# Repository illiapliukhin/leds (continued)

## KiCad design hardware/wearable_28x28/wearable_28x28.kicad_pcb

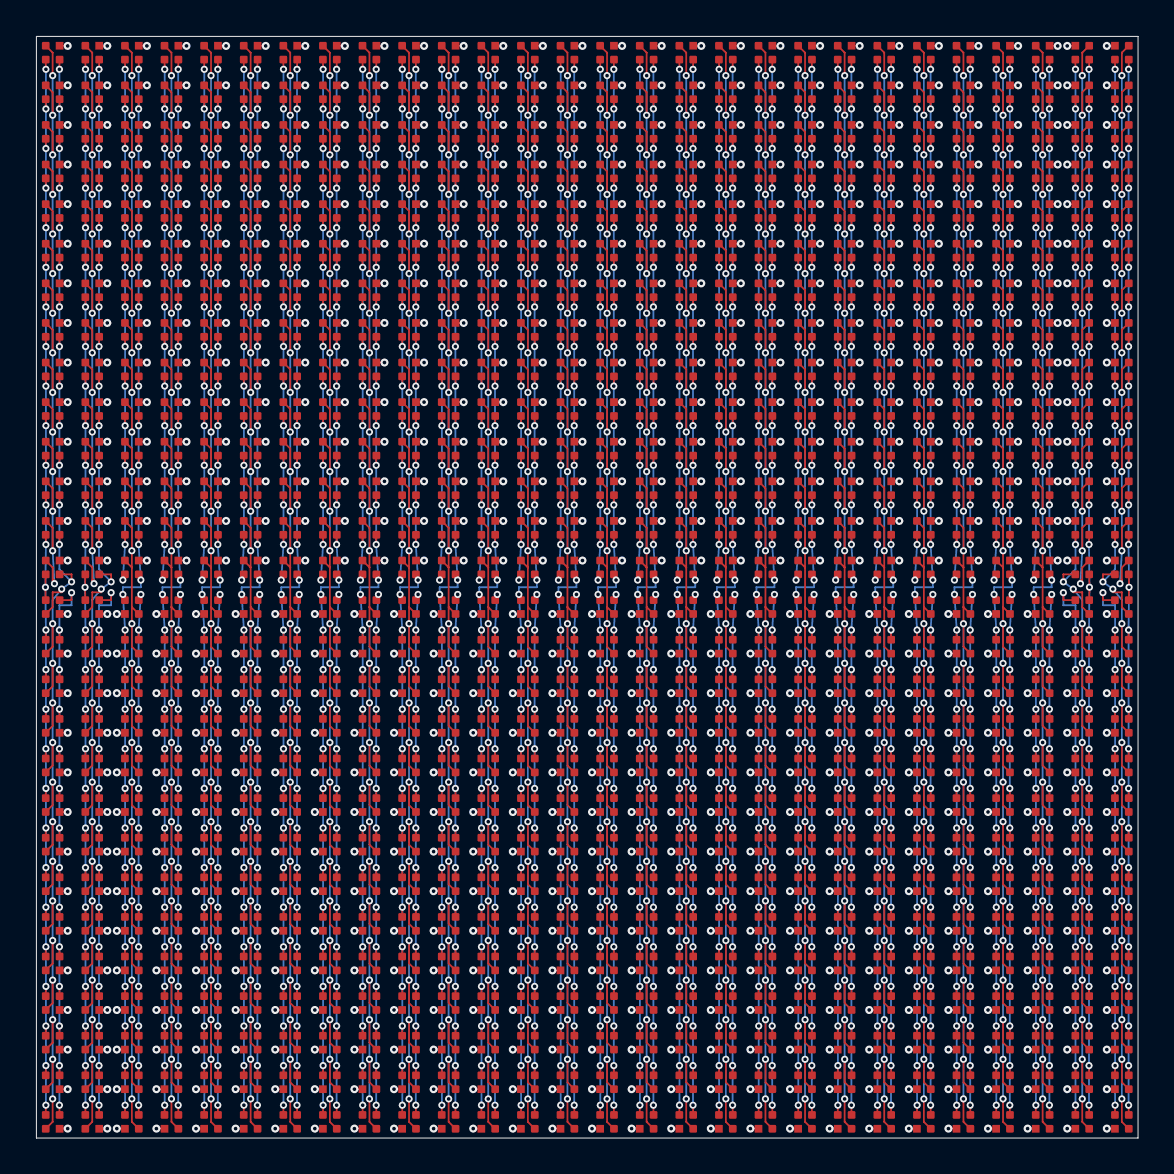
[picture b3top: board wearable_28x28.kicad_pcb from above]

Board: 4 copper layers, 61.2 x 61.2 mm, 784 parts (0 on the bottom side), 112 nets.

Parts:
D1, D2, D3, D4, D5, D6, D7, D8, D9, D10, D11, D12, D13, D14, D15, D16, D17, D18, D19, D20, D21, D22, D23, D24, D25, D26, D27, D28, D29, D30, D31, D32, D33, D34, D35, D36, D37, D38, D39, D40, D41, D42, D43, D44, D45, D46, D47, D48, D49, D50, D51, D52, D53, D54, D55, D56, D57, D58, D59, D60, D61, D62, D63, D64, D65, D66, D67, D68, D69, D70, D71, D72, D73, D74, D75, D76, D77, D78, D79, D80, D81, D82, D83, D84, D85, D86, D87, D88, D89, D90, D91, D92, D93, D94, D95, D96, D97, D98, D99, D100, D101, D102, D103, D104, D105, D106, D107, D108, D109, D110, D111, D112, D113, D114, D115, D116, D117, D118, D119, D120, D121, D122, D123, D124, D125, D126, D127, D128, D129, D130, D131, D132, D133, D134, D135, D136, D137, D138, D139, D140, D141, D142, D143, D144, D145, D146, D147, D148, D149, D150, D151, D152, D153, D154, D155, D156, D157, D158, D159, D160, D161, D162, D163, D164, D165, D166, D167, D168, D169, D170, D171, D172, D173, D174, D175, D176, D177, D178, D179, D180, D181, D182, D183, D184, D185, D186, D187, D188, D189, D190, D191, D192, D193, D194, D195, D196, D197, D198, D199, D200, D201, D202, D203, D204, D205, D206, D207, D208, D209, D210, D211, D212, D213, D214, D215, D216, D217, D218, D219, D220, D221, D222, D223, D224, D225, D226, D227, D228, D229, D230, D231, D232, D233, D234, D235, D236, D237, D238, D239, D240, D241, D242, D243, D244, D245, D246, D247, D248, D249, D250, D251, D252, D253, D254, D255, D256, D257, D258, D259, D260, D261, D262, D263, D264, D265, D266, D267, D268, D269, D270, D271, D272, D273, D274, D275, D276, D277, D278, D279, D280, D281, D282, D283, D284, D285, D286, D287, D288, D289, D290, D291, D292, D293, D294, D295, D296, D297, D298, D299, D300, D301, D302, D303, D304, D305, D306, D307, D308, D309, D310, D311, D312, D313, D314, D315, D316, D317, D318, D319, D320, D321, D322, D323, D324, D325, D326, D327, D328, D329, D330, D331, D332, D333, D334, D335, D336, D337, D338, D339, D340, D341, D342, D343, D344, D345, D346, D347, D348, D349, D350, D351, D352, D353, D354, D355, D356, D357, D358, D359, D360, D361, D362, D363, D364, D365, D366, D367, D368, D369, D370, D371, D372, D373, D374, D375, D376, D377, D378, D379, D380, D381, D382, D383, D384, D385, D386, D387, D388, D389, D390, D391, D392, D393, D394, D395, D396, D397, D398, D399, D400, D401, D402, D403, D404, D405, D406, D407, D408, D409, D410, D411, D412, D413, D414, D415, D416, D417, D418, D419, D420, D421, D422, D423, D424, D425, D426, D427, D428, D429, D430, D431, D432, D433, D434, D435, D436, D437, D438, D439, D440, D441, D442, D443, D444, D445, D446, D447, D448, D449, D450, D451, D452, D453, D454, D455, D456, D457, D458, D459, D460, D461, D462, D463, D464, D465, D466, D467, D468, D469, D470, D471, D472, D473, D474, D475, D476, D477, D478, D479, D480, D481, D482, D483, D484, D485, D486, D487, D488, D489, D490, D491, D492, D493, D494, D495, D496, D497, D498, D499, D500, D501, D502, D503, D504, D505, D506, D507, D508, D509, D510, D511, D512, D513, D514, D515, D516, D517, D518, D519, D520, D521, D522, D523, D524, D525, D526, D527, D528, D529, D530, D531, D532, D533, D534, D535, D536, D537, D538, D539, D540, D541, D542, D543, D544, D545, D546, D547, D548, D549, D550, D551, D552, D553, D554, D555, D556, D557, D558, D559, D560, D561, D562, D563, D564, D565, D566, D567, D568, D569, D570, D571, D572, D573, D574, D575, D576, D577, D578, D579, D580, D581, D582, D583, D584, D585, D586, D587, D588, D589, D590, D591, D592, D593, D594, D595, D596, D597, D598, D599, D600, D601, D602, D603, D604, D605, D606, D607, D608, D609, D610, D611, D612, D613, D614, D615, D616, D617, D618, D619, D620, D621, D622, D623, D624, D625, D626, D627, D628, D629, D630, D631, D632, D633, D634, D635, D636, D637, D638, D639, D640, D641, D642, D643, D644, D645, D646, D647, D648, D649, D650, D651, D652, D653, D654, D655, D656, D657, D658, D659, D660, D661, D662, D663, D664, D665, D666, D667, D668, D669, D670, D671, D672, D673, D674, D675, D676, D677, D678, D679, D680, D681, D682, D683, D684, D685, D686, D687, D688, D689, D690, D691, D692, D693, D694, D695, D696, D697, D698, D699, D700, D701, D702, D703, D704, D705, D706, D707, D708, D709, D710, D711, D712, D713, D714, D715, D716, D717, D718, D719, D720, D721, D722, D723, D724, D725, D726, D727, D728, D729, D730, D731, D732, D733, D734, D735, D736, D737, D738, D739, D740, D741, D742, D743, D744, D745, D746, D747, D748, D749, D750, D751, D752, D753, D754, D755, D756, D757, D758, D759, D760, D761, D762, D763, D764, D765, D766, D767, D768, D769, D770, D771, D772, D773, D774, D775, D776, D777, D778, D779, D780, D781, D782, D783, D784: MHPA1010RGBDT

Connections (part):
COL_B_01: D1.4 (K_B), D29.4 (K_B), D57.4 (K_B), D85.4 (K_B), D113.4 (K_B), D141.4 (K_B), D169.4 (K_B), D197.4 (K_B), D225.4 (K_B), D253.4 (K_B), D281.4 (K_B), D309.4 (K_B), D337.4 (K_B), D365.4 (K_B), D393.4 (K_B), D421.4 (K_B), D449.4 (K_B), D477.4 (K_B), D505.4 (K_B), D533.4 (K_B), D561.4 (K_B), D589.4 (K_B), D617.4 (K_B), D645.4 (K_B), D673.4 (K_B), D701.4 (K_B), D729.4 (K_B), D757.4 (K_B)
COL_B_02: D2.4 (K_B), D30.4 (K_B), D58.4 (K_B), D86.4 (K_B), D114.4 (K_B), D142.4 (K_B), D170.4 (K_B), D198.4 (K_B), D226.4 (K_B), D254.4 (K_B), D282.4 (K_B), D310.4 (K_B), D338.4 (K_B), D366.4 (K_B), D394.4 (K_B), D422.4 (K_B), D450.4 (K_B), D478.4 (K_B), D506.4 (K_B), D534.4 (K_B), D562.4 (K_B), D590.4 (K_B), D618.4 (K_B), D646.4 (K_B), D674.4 (K_B), D702.4 (K_B), D730.4 (K_B), D758.4 (K_B)
COL_B_03: D3.4 (K_B), D31.4 (K_B), D59.4 (K_B), D87.4 (K_B), D115.4 (K_B), D143.4 (K_B), D171.4 (K_B), D199.4 (K_B), D227.4 (K_B), D255.4 (K_B), D283.4 (K_B), D311.4 (K_B), D339.4 (K_B), D367.4 (K_B), D395.4 (K_B), D423.4 (K_B), D451.4 (K_B), D479.4 (K_B), D507.4 (K_B), D535.4 (K_B), D563.4 (K_B), D591.4 (K_B), D619.4 (K_B), D647.4 (K_B), D675.4 (K_B), D703.4 (K_B), D731.4 (K_B), D759.4 (K_B)
COL_B_04: D4.4 (K_B), D32.4 (K_B), D60.4 (K_B), D88.4 (K_B), D116.4 (K_B), D144.4 (K_B), D172.4 (K_B), D200.4 (K_B), D228.4 (K_B), D256.4 (K_B), D284.4 (K_B), D312.4 (K_B), D340.4 (K_B), D368.4 (K_B), D396.4 (K_B), D424.4 (K_B), D452.4 (K_B), D480.4 (K_B), D508.4 (K_B), D536.4 (K_B), D564.4 (K_B), D592.4 (K_B), D620.4 (K_B), D648.4 (K_B), D676.4 (K_B), D704.4 (K_B), D732.4 (K_B), D760.4 (K_B)
COL_B_05: D5.4 (K_B), D33.4 (K_B), D61.4 (K_B), D89.4 (K_B), D117.4 (K_B), D145.4 (K_B), D173.4 (K_B), D201.4 (K_B), D229.4 (K_B), D257.4 (K_B), D285.4 (K_B), D313.4 (K_B), D341.4 (K_B), D369.4 (K_B), D397.4 (K_B), D425.4 (K_B), D453.4 (K_B), D481.4 (K_B), D509.4 (K_B), D537.4 (K_B), D565.4 (K_B), D593.4 (K_B), D621.4 (K_B), D649.4 (K_B), D677.4 (K_B), D705.4 (K_B), D733.4 (K_B), D761.4 (K_B)
COL_B_06: D6.4 (K_B), D34.4 (K_B), D62.4 (K_B), D90.4 (K_B), D118.4 (K_B), D146.4 (K_B), D174.4 (K_B), D202.4 (K_B), D230.4 (K_B), D258.4 (K_B), D286.4 (K_B), D314.4 (K_B), D342.4 (K_B), D370.4 (K_B), D398.4 (K_B), D426.4 (K_B), D454.4 (K_B), D482.4 (K_B), D510.4 (K_B), D538.4 (K_B), D566.4 (K_B), D594.4 (K_B), D622.4 (K_B), D650.4 (K_B), D678.4 (K_B), D706.4 (K_B), D734.4 (K_B), D762.4 (K_B)
COL_B_07: D7.4 (K_B), D35.4 (K_B), D63.4 (K_B), D91.4 (K_B), D119.4 (K_B), D147.4 (K_B), D175.4 (K_B), D203.4 (K_B), D231.4 (K_B), D259.4 (K_B), D287.4 (K_B), D315.4 (K_B), D343.4 (K_B), D371.4 (K_B), D399.4 (K_B), D427.4 (K_B), D455.4 (K_B), D483.4 (K_B), D511.4 (K_B), D539.4 (K_B), D567.4 (K_B), D595.4 (K_B), D623.4 (K_B), D651.4 (K_B), D679.4 (K_B), D707.4 (K_B), D735.4 (K_B), D763.4 (K_B)
COL_B_08: D8.4 (K_B), D36.4 (K_B), D64.4 (K_B), D92.4 (K_B), D120.4 (K_B), D148.4 (K_B), D176.4 (K_B), D204.4 (K_B), D232.4 (K_B), D260.4 (K_B), D288.4 (K_B), D316.4 (K_B), D344.4 (K_B), D372.4 (K_B), D400.4 (K_B), D428.4 (K_B), D456.4 (K_B), D484.4 (K_B), D512.4 (K_B), D540.4 (K_B), D568.4 (K_B), D596.4 (K_B), D624.4 (K_B), D652.4 (K_B), D680.4 (K_B), D708.4 (K_B), D736.4 (K_B), D764.4 (K_B)
COL_B_09: D9.4 (K_B), D37.4 (K_B), D65.4 (K_B), D93.4 (K_B), D121.4 (K_B), D149.4 (K_B), D177.4 (K_B), D205.4 (K_B), D233.4 (K_B), D261.4 (K_B), D289.4 (K_B), D317.4 (K_B), D345.4 (K_B), D373.4 (K_B), D401.4 (K_B), D429.4 (K_B), D457.4 (K_B), D485.4 (K_B), D513.4 (K_B), D541.4 (K_B), D569.4 (K_B), D597.4 (K_B), D625.4 (K_B), D653.4 (K_B), D681.4 (K_B), D709.4 (K_B), D737.4 (K_B), D765.4 (K_B)
COL_B_10: D10.4 (K_B), D38.4 (K_B), D66.4 (K_B), D94.4 (K_B), D122.4 (K_B), D150.4 (K_B), D178.4 (K_B), D206.4 (K_B), D234.4 (K_B), D262.4 (K_B), D290.4 (K_B), D318.4 (K_B), D346.4 (K_B), D374.4 (K_B), D402.4 (K_B), D430.4 (K_B), D458.4 (K_B), D486.4 (K_B), D514.4 (K_B), D542.4 (K_B), D570.4 (K_B), D598.4 (K_B), D626.4 (K_B), D654.4 (K_B), D682.4 (K_B), D710.4 (K_B), D738.4 (K_B), D766.4 (K_B)
COL_B_11: D11.4 (K_B), D39.4 (K_B), D67.4 (K_B), D95.4 (K_B), D123.4 (K_B), D151.4 (K_B), D179.4 (K_B), D207.4 (K_B), D235.4 (K_B), D263.4 (K_B), D291.4 (K_B), D319.4 (K_B), D347.4 (K_B), D375.4 (K_B), D403.4 (K_B), D431.4 (K_B), D459.4 (K_B), D487.4 (K_B), D515.4 (K_B), D543.4 (K_B), D571.4 (K_B), D599.4 (K_B), D627.4 (K_B), D655.4 (K_B), D683.4 (K_B), D711.4 (K_B), D739.4 (K_B), D767.4 (K_B)
COL_B_12: D12.4 (K_B), D40.4 (K_B), D68.4 (K_B), D96.4 (K_B), D124.4 (K_B), D152.4 (K_B), D180.4 (K_B), D208.4 (K_B), D236.4 (K_B), D264.4 (K_B), D292.4 (K_B), D320.4 (K_B), D348.4 (K_B), D376.4 (K_B), D404.4 (K_B), D432.4 (K_B), D460.4 (K_B), D488.4 (K_B), D516.4 (K_B), D544.4 (K_B), D572.4 (K_B), D600.4 (K_B), D628.4 (K_B), D656.4 (K_B), D684.4 (K_B), D712.4 (K_B), D740.4 (K_B), D768.4 (K_B)
COL_B_13: D13.4 (K_B), D41.4 (K_B), D69.4 (K_B), D97.4 (K_B), D125.4 (K_B), D153.4 (K_B), D181.4 (K_B), D209.4 (K_B), D237.4 (K_B), D265.4 (K_B), D293.4 (K_B), D321.4 (K_B), D349.4 (K_B), D377.4 (K_B), D405.4 (K_B), D433.4 (K_B), D461.4 (K_B), D489.4 (K_B), D517.4 (K_B), D545.4 (K_B), D573.4 (K_B), D601.4 (K_B), D629.4 (K_B), D657.4 (K_B), D685.4 (K_B), D713.4 (K_B), D741.4 (K_B), D769.4 (K_B)
COL_B_14: D14.4 (K_B), D42.4 (K_B), D70.4 (K_B), D98.4 (K_B), D126.4 (K_B), D154.4 (K_B), D182.4 (K_B), D210.4 (K_B), D238.4 (K_B), D266.4 (K_B), D294.4 (K_B), D322.4 (K_B), D350.4 (K_B), D378.4 (K_B), D406.4 (K_B), D434.4 (K_B), D462.4 (K_B), D490.4 (K_B), D518.4 (K_B), D546.4 (K_B), D574.4 (K_B), D602.4 (K_B), D630.4 (K_B), D658.4 (K_B), D686.4 (K_B), D714.4 (K_B), D742.4 (K_B), D770.4 (K_B)
COL_B_15: D15.4 (K_B), D43.4 (K_B), D71.4 (K_B), D99.4 (K_B), D127.4 (K_B), D155.4 (K_B), D183.4 (K_B), D211.4 (K_B), D239.4 (K_B), D267.4 (K_B), D295.4 (K_B), D323.4 (K_B), D351.4 (K_B), D379.4 (K_B), D407.4 (K_B), D435.4 (K_B), D463.4 (K_B), D491.4 (K_B), D519.4 (K_B), D547.4 (K_B), D575.4 (K_B), D603.4 (K_B), D631.4 (K_B), D659.4 (K_B), D687.4 (K_B), D715.4 (K_B), D743.4 (K_B), D771.4 (K_B)
COL_B_16: D16.4 (K_B), D44.4 (K_B), D72.4 (K_B), D100.4 (K_B), D128.4 (K_B), D156.4 (K_B), D184.4 (K_B), D212.4 (K_B), D240.4 (K_B), D268.4 (K_B), D296.4 (K_B), D324.4 (K_B), D352.4 (K_B), D380.4 (K_B), D408.4 (K_B), D436.4 (K_B), D464.4 (K_B), D492.4 (K_B), D520.4 (K_B), D548.4 (K_B), D576.4 (K_B), D604.4 (K_B), D632.4 (K_B), D660.4 (K_B), D688.4 (K_B), D716.4 (K_B), D744.4 (K_B), D772.4 (K_B)
COL_B_17: D17.4 (K_B), D45.4 (K_B), D73.4 (K_B), D101.4 (K_B), D129.4 (K_B), D157.4 (K_B), D185.4 (K_B), D213.4 (K_B), D241.4 (K_B), D269.4 (K_B), D297.4 (K_B), D325.4 (K_B), D353.4 (K_B), D381.4 (K_B), D409.4 (K_B), D437.4 (K_B), D465.4 (K_B), D493.4 (K_B), D521.4 (K_B), D549.4 (K_B), D577.4 (K_B), D605.4 (K_B), D633.4 (K_B), D661.4 (K_B), D689.4 (K_B), D717.4 (K_B), D745.4 (K_B), D773.4 (K_B)
COL_B_18: D18.4 (K_B), D46.4 (K_B), D74.4 (K_B), D102.4 (K_B), D130.4 (K_B), D158.4 (K_B), D186.4 (K_B), D214.4 (K_B), D242.4 (K_B), D270.4 (K_B), D298.4 (K_B), D326.4 (K_B), D354.4 (K_B), D382.4 (K_B), D410.4 (K_B), D438.4 (K_B), D466.4 (K_B), D494.4 (K_B), D522.4 (K_B), D550.4 (K_B), D578.4 (K_B), D606.4 (K_B), D634.4 (K_B), D662.4 (K_B), D690.4 (K_B), D718.4 (K_B), D746.4 (K_B), D774.4 (K_B)
COL_B_19: D19.4 (K_B), D47.4 (K_B), D75.4 (K_B), D103.4 (K_B), D131.4 (K_B), D159.4 (K_B), D187.4 (K_B), D215.4 (K_B), D243.4 (K_B), D271.4 (K_B), D299.4 (K_B), D327.4 (K_B), D355.4 (K_B), D383.4 (K_B), D411.4 (K_B), D439.4 (K_B), D467.4 (K_B), D495.4 (K_B), D523.4 (K_B), D551.4 (K_B), D579.4 (K_B), D607.4 (K_B), D635.4 (K_B), D663.4 (K_B), D691.4 (K_B), D719.4 (K_B), D747.4 (K_B), D775.4 (K_B)
COL_B_20: D20.4 (K_B), D48.4 (K_B), D76.4 (K_B), D104.4 (K_B), D132.4 (K_B), D160.4 (K_B), D188.4 (K_B), D216.4 (K_B), D244.4 (K_B), D272.4 (K_B), D300.4 (K_B), D328.4 (K_B), D356.4 (K_B), D384.4 (K_B), D412.4 (K_B), D440.4 (K_B), D468.4 (K_B), D496.4 (K_B), D524.4 (K_B), D552.4 (K_B), D580.4 (K_B), D608.4 (K_B), D636.4 (K_B), D664.4 (K_B), D692.4 (K_B), D720.4 (K_B), D748.4 (K_B), D776.4 (K_B)
COL_B_21: D21.4 (K_B), D49.4 (K_B), D77.4 (K_B), D105.4 (K_B), D133.4 (K_B), D161.4 (K_B), D189.4 (K_B), D217.4 (K_B), D245.4 (K_B), D273.4 (K_B), D301.4 (K_B), D329.4 (K_B), D357.4 (K_B), D385.4 (K_B), D413.4 (K_B), D441.4 (K_B), D469.4 (K_B), D497.4 (K_B), D525.4 (K_B), D553.4 (K_B), D581.4 (K_B), D609.4 (K_B), D637.4 (K_B), D665.4 (K_B), D693.4 (K_B), D721.4 (K_B), D749.4 (K_B), D777.4 (K_B)
COL_B_22: D22.4 (K_B), D50.4 (K_B), D78.4 (K_B), D106.4 (K_B), D134.4 (K_B), D162.4 (K_B), D190.4 (K_B), D218.4 (K_B), D246.4 (K_B), D274.4 (K_B), D302.4 (K_B), D330.4 (K_B), D358.4 (K_B), D386.4 (K_B), D414.4 (K_B), D442.4 (K_B), D470.4 (K_B), D498.4 (K_B), D526.4 (K_B), D554.4 (K_B), D582.4 (K_B), D610.4 (K_B), D638.4 (K_B), D666.4 (K_B), D694.4 (K_B), D722.4 (K_B), D750.4 (K_B), D778.4 (K_B)
COL_B_23: D23.4 (K_B), D51.4 (K_B), D79.4 (K_B), D107.4 (K_B), D135.4 (K_B), D163.4 (K_B), D191.4 (K_B), D219.4 (K_B), D247.4 (K_B), D275.4 (K_B), D303.4 (K_B), D331.4 (K_B), D359.4 (K_B), D387.4 (K_B), D415.4 (K_B), D443.4 (K_B), D471.4 (K_B), D499.4 (K_B), D527.4 (K_B), D555.4 (K_B), D583.4 (K_B), D611.4 (K_B), D639.4 (K_B), D667.4 (K_B), D695.4 (K_B), D723.4 (K_B), D751.4 (K_B), D779.4 (K_B)
COL_B_24: D24.4 (K_B), D52.4 (K_B), D80.4 (K_B), D108.4 (K_B), D136.4 (K_B), D164.4 (K_B), D192.4 (K_B), D220.4 (K_B), D248.4 (K_B), D276.4 (K_B), D304.4 (K_B), D332.4 (K_B), D360.4 (K_B), D388.4 (K_B), D416.4 (K_B), D444.4 (K_B), D472.4 (K_B), D500.4 (K_B), D528.4 (K_B), D556.4 (K_B), D584.4 (K_B), D612.4 (K_B), D640.4 (K_B), D668.4 (K_B), D696.4 (K_B), D724.4 (K_B), D752.4 (K_B), D780.4 (K_B)
COL_B_25: D25.4 (K_B), D53.4 (K_B), D81.4 (K_B), D109.4 (K_B), D137.4 (K_B), D165.4 (K_B), D193.4 (K_B), D221.4 (K_B), D249.4 (K_B), D277.4 (K_B), D305.4 (K_B), D333.4 (K_B), D361.4 (K_B), D389.4 (K_B), D417.4 (K_B), D445.4 (K_B), D473.4 (K_B), D501.4 (K_B), D529.4 (K_B), D557.4 (K_B), D585.4 (K_B), D613.4 (K_B), D641.4 (K_B), D669.4 (K_B), D697.4 (K_B), D725.4 (K_B), D753.4 (K_B), D781.4 (K_B)
COL_B_26: D26.4 (K_B), D54.4 (K_B), D82.4 (K_B), D110.4 (K_B), D138.4 (K_B), D166.4 (K_B), D194.4 (K_B), D222.4 (K_B), D250.4 (K_B), D278.4 (K_B), D306.4 (K_B), D334.4 (K_B), D362.4 (K_B), D390.4 (K_B), D418.4 (K_B), D446.4 (K_B), D474.4 (K_B), D502.4 (K_B), D530.4 (K_B), D558.4 (K_B), D586.4 (K_B), D614.4 (K_B), D642.4 (K_B), D670.4 (K_B), D698.4 (K_B), D726.4 (K_B), D754.4 (K_B), D782.4 (K_B)
COL_B_27: D27.4 (K_B), D55.4 (K_B), D83.4 (K_B), D111.4 (K_B), D139.4 (K_B), D167.4 (K_B), D195.4 (K_B), D223.4 (K_B), D251.4 (K_B), D279.4 (K_B), D307.4 (K_B), D335.4 (K_B), D363.4 (K_B), D391.4 (K_B), D419.4 (K_B), D447.4 (K_B), D475.4 (K_B), D503.4 (K_B), D531.4 (K_B), D559.4 (K_B), D587.4 (K_B), D615.4 (K_B), D643.4 (K_B), D671.4 (K_B), D699.4 (K_B), D727.4 (K_B), D755.4 (K_B), D783.4 (K_B)
COL_B_28: D28.4 (K_B), D56.4 (K_B), D84.4 (K_B), D112.4 (K_B), D140.4 (K_B), D168.4 (K_B), D196.4 (K_B), D224.4 (K_B), D252.4 (K_B), D280.4 (K_B), D308.4 (K_B), D336.4 (K_B), D364.4 (K_B), D392.4 (K_B), D420.4 (K_B), D448.4 (K_B), D476.4 (K_B), D504.4 (K_B), D532.4 (K_B), D560.4 (K_B), D588.4 (K_B), D616.4 (K_B), D644.4 (K_B), D672.4 (K_B), D700.4 (K_B), D728.4 (K_B), D756.4 (K_B), D784.4 (K_B)
COL_G_01: D1.3 (K_G), D29.3 (K_G), D57.3 (K_G), D85.3 (K_G), D113.3 (K_G), D141.3 (K_G), D169.3 (K_G), D197.3 (K_G), D225.3 (K_G), D253.3 (K_G), D281.3 (K_G), D309.3 (K_G), D337.3 (K_G), D365.3 (K_G), D393.3 (K_G), D421.3 (K_G), D449.3 (K_G), D477.3 (K_G), D505.3 (K_G), D533.3 (K_G), D561.3 (K_G), D589.3 (K_G), D617.3 (K_G), D645.3 (K_G), D673.3 (K_G), D701.3 (K_G), D729.3 (K_G), D757.3 (K_G)
COL_G_02: D2.3 (K_G), D30.3 (K_G), D58.3 (K_G), D86.3 (K_G), D114.3 (K_G), D142.3 (K_G), D170.3 (K_G), D198.3 (K_G), D226.3 (K_G), D254.3 (K_G), D282.3 (K_G), D310.3 (K_G), D338.3 (K_G), D366.3 (K_G), D394.3 (K_G), D422.3 (K_G), D450.3 (K_G), D478.3 (K_G), D506.3 (K_G), D534.3 (K_G), D562.3 (K_G), D590.3 (K_G), D618.3 (K_G), D646.3 (K_G), D674.3 (K_G), D702.3 (K_G), D730.3 (K_G), D758.3 (K_G)
COL_G_03: D3.3 (K_G), D31.3 (K_G), D59.3 (K_G), D87.3 (K_G), D115.3 (K_G), D143.3 (K_G), D171.3 (K_G), D199.3 (K_G), D227.3 (K_G), D255.3 (K_G), D283.3 (K_G), D311.3 (K_G), D339.3 (K_G), D367.3 (K_G), D395.3 (K_G), D423.3 (K_G), D451.3 (K_G), D479.3 (K_G), D507.3 (K_G), D535.3 (K_G), D563.3 (K_G), D591.3 (K_G), D619.3 (K_G), D647.3 (K_G), D675.3 (K_G), D703.3 (K_G), D731.3 (K_G), D759.3 (K_G)
COL_G_04: D4.3 (K_G), D32.3 (K_G), D60.3 (K_G), D88.3 (K_G), D116.3 (K_G), D144.3 (K_G), D172.3 (K_G), D200.3 (K_G), D228.3 (K_G), D256.3 (K_G), D284.3 (K_G), D312.3 (K_G), D340.3 (K_G), D368.3 (K_G), D396.3 (K_G), D424.3 (K_G), D452.3 (K_G), D480.3 (K_G), D508.3 (K_G), D536.3 (K_G), D564.3 (K_G), D592.3 (K_G), D620.3 (K_G), D648.3 (K_G), D676.3 (K_G), D704.3 (K_G), D732.3 (K_G), D760.3 (K_G)
COL_G_05: D5.3 (K_G), D33.3 (K_G), D61.3 (K_G), D89.3 (K_G), D117.3 (K_G), D145.3 (K_G), D173.3 (K_G), D201.3 (K_G), D229.3 (K_G), D257.3 (K_G), D285.3 (K_G), D313.3 (K_G), D341.3 (K_G), D369.3 (K_G), D397.3 (K_G), D425.3 (K_G), D453.3 (K_G), D481.3 (K_G), D509.3 (K_G), D537.3 (K_G), D565.3 (K_G), D593.3 (K_G), D621.3 (K_G), D649.3 (K_G), D677.3 (K_G), D705.3 (K_G), D733.3 (K_G), D761.3 (K_G)
COL_G_06: D6.3 (K_G), D34.3 (K_G), D62.3 (K_G), D90.3 (K_G), D118.3 (K_G), D146.3 (K_G), D174.3 (K_G), D202.3 (K_G), D230.3 (K_G), D258.3 (K_G), D286.3 (K_G), D314.3 (K_G), D342.3 (K_G), D370.3 (K_G), D398.3 (K_G), D426.3 (K_G), D454.3 (K_G), D482.3 (K_G), D510.3 (K_G), D538.3 (K_G), D566.3 (K_G), D594.3 (K_G), D622.3 (K_G), D650.3 (K_G), D678.3 (K_G), D706.3 (K_G), D734.3 (K_G), D762.3 (K_G)
COL_G_07: D7.3 (K_G), D35.3 (K_G), D63.3 (K_G), D91.3 (K_G), D119.3 (K_G), D147.3 (K_G), D175.3 (K_G), D203.3 (K_G), D231.3 (K_G), D259.3 (K_G), D287.3 (K_G), D315.3 (K_G), D343.3 (K_G), D371.3 (K_G), D399.3 (K_G), D427.3 (K_G), D455.3 (K_G), D483.3 (K_G), D511.3 (K_G), D539.3 (K_G), D567.3 (K_G), D595.3 (K_G), D623.3 (K_G), D651.3 (K_G), D679.3 (K_G), D707.3 (K_G), D735.3 (K_G), D763.3 (K_G)
COL_G_08: D8.3 (K_G), D36.3 (K_G), D64.3 (K_G), D92.3 (K_G), D120.3 (K_G), D148.3 (K_G), D176.3 (K_G), D204.3 (K_G), D232.3 (K_G), D260.3 (K_G), D288.3 (K_G), D316.3 (K_G), D344.3 (K_G), D372.3 (K_G), D400.3 (K_G), D428.3 (K_G), D456.3 (K_G), D484.3 (K_G), D512.3 (K_G), D540.3 (K_G), D568.3 (K_G), D596.3 (K_G), D624.3 (K_G), D652.3 (K_G), D680.3 (K_G), D708.3 (K_G), D736.3 (K_G), D764.3 (K_G)
COL_G_09: D9.3 (K_G), D37.3 (K_G), D65.3 (K_G), D93.3 (K_G), D121.3 (K_G), D149.3 (K_G), D177.3 (K_G), D205.3 (K_G), D233.3 (K_G), D261.3 (K_G), D289.3 (K_G), D317.3 (K_G), D345.3 (K_G), D373.3 (K_G), D401.3 (K_G), D429.3 (K_G), D457.3 (K_G), D485.3 (K_G), D513.3 (K_G), D541.3 (K_G), D569.3 (K_G), D597.3 (K_G), D625.3 (K_G), D653.3 (K_G), D681.3 (K_G), D709.3 (K_G), D737.3 (K_G), D765.3 (K_G)
COL_G_10: D10.3 (K_G), D38.3 (K_G), D66.3 (K_G), D94.3 (K_G), D122.3 (K_G), D150.3 (K_G), D178.3 (K_G), D206.3 (K_G), D234.3 (K_G), D262.3 (K_G), D290.3 (K_G), D318.3 (K_G), D346.3 (K_G), D374.3 (K_G), D402.3 (K_G), D430.3 (K_G), D458.3 (K_G), D486.3 (K_G), D514.3 (K_G), D542.3 (K_G), D570.3 (K_G), D598.3 (K_G), D626.3 (K_G), D654.3 (K_G), D682.3 (K_G), D710.3 (K_G), D738.3 (K_G), D766.3 (K_G)
COL_G_11: D11.3 (K_G), D39.3 (K_G), D67.3 (K_G), D95.3 (K_G), D123.3 (K_G), D151.3 (K_G), D179.3 (K_G), D207.3 (K_G), D235.3 (K_G), D263.3 (K_G), D291.3 (K_G), D319.3 (K_G), D347.3 (K_G), D375.3 (K_G), D403.3 (K_G), D431.3 (K_G), D459.3 (K_G), D487.3 (K_G), D515.3 (K_G), D543.3 (K_G), D571.3 (K_G), D599.3 (K_G), D627.3 (K_G), D655.3 (K_G), D683.3 (K_G), D711.3 (K_G), D739.3 (K_G), D767.3 (K_G)
COL_G_12: D12.3 (K_G), D40.3 (K_G), D68.3 (K_G), D96.3 (K_G), D124.3 (K_G), D152.3 (K_G), D180.3 (K_G), D208.3 (K_G), D236.3 (K_G), D264.3 (K_G), D292.3 (K_G), D320.3 (K_G), D348.3 (K_G), D376.3 (K_G), D404.3 (K_G), D432.3 (K_G), D460.3 (K_G), D488.3 (K_G), D516.3 (K_G), D544.3 (K_G), D572.3 (K_G), D600.3 (K_G), D628.3 (K_G), D656.3 (K_G), D684.3 (K_G), D712.3 (K_G), D740.3 (K_G), D768.3 (K_G)
COL_G_13: D13.3 (K_G), D41.3 (K_G), D69.3 (K_G), D97.3 (K_G), D125.3 (K_G), D153.3 (K_G), D181.3 (K_G), D209.3 (K_G), D237.3 (K_G), D265.3 (K_G), D293.3 (K_G), D321.3 (K_G), D349.3 (K_G), D377.3 (K_G), D405.3 (K_G), D433.3 (K_G), D461.3 (K_G), D489.3 (K_G), D517.3 (K_G), D545.3 (K_G), D573.3 (K_G), D601.3 (K_G), D629.3 (K_G), D657.3 (K_G), D685.3 (K_G), D713.3 (K_G), D741.3 (K_G), D769.3 (K_G)
COL_G_14: D14.3 (K_G), D42.3 (K_G), D70.3 (K_G), D98.3 (K_G), D126.3 (K_G), D154.3 (K_G), D182.3 (K_G), D210.3 (K_G), D238.3 (K_G), D266.3 (K_G), D294.3 (K_G), D322.3 (K_G), D350.3 (K_G), D378.3 (K_G), D406.3 (K_G), D434.3 (K_G), D462.3 (K_G), D490.3 (K_G), D518.3 (K_G), D546.3 (K_G), D574.3 (K_G), D602.3 (K_G), D630.3 (K_G), D658.3 (K_G), D686.3 (K_G), D714.3 (K_G), D742.3 (K_G), D770.3 (K_G)
COL_G_15: D15.3 (K_G), D43.3 (K_G), D71.3 (K_G), D99.3 (K_G), D127.3 (K_G), D155.3 (K_G), D183.3 (K_G), D211.3 (K_G), D239.3 (K_G), D267.3 (K_G), D295.3 (K_G), D323.3 (K_G), D351.3 (K_G), D379.3 (K_G), D407.3 (K_G), D435.3 (K_G), D463.3 (K_G), D491.3 (K_G), D519.3 (K_G), D547.3 (K_G), D575.3 (K_G), D603.3 (K_G), D631.3 (K_G), D659.3 (K_G), D687.3 (K_G), D715.3 (K_G), D743.3 (K_G), D771.3 (K_G)
COL_G_16: D16.3 (K_G), D44.3 (K_G), D72.3 (K_G), D100.3 (K_G), D128.3 (K_G), D156.3 (K_G), D184.3 (K_G), D212.3 (K_G), D240.3 (K_G), D268.3 (K_G), D296.3 (K_G), D324.3 (K_G), D352.3 (K_G), D380.3 (K_G), D408.3 (K_G), D436.3 (K_G), D464.3 (K_G), D492.3 (K_G), D520.3 (K_G), D548.3 (K_G), D576.3 (K_G), D604.3 (K_G), D632.3 (K_G), D660.3 (K_G), D688.3 (K_G), D716.3 (K_G), D744.3 (K_G), D772.3 (K_G)
COL_G_17: D17.3 (K_G), D45.3 (K_G), D73.3 (K_G), D101.3 (K_G), D129.3 (K_G), D157.3 (K_G), D185.3 (K_G), D213.3 (K_G), D241.3 (K_G), D269.3 (K_G), D297.3 (K_G), D325.3 (K_G), D353.3 (K_G), D381.3 (K_G), D409.3 (K_G), D437.3 (K_G), D465.3 (K_G), D493.3 (K_G), D521.3 (K_G), D549.3 (K_G), D577.3 (K_G), D605.3 (K_G), D633.3 (K_G), D661.3 (K_G), D689.3 (K_G), D717.3 (K_G), D745.3 (K_G), D773.3 (K_G)
COL_G_18: D18.3 (K_G), D46.3 (K_G), D74.3 (K_G), D102.3 (K_G), D130.3 (K_G), D158.3 (K_G), D186.3 (K_G), D214.3 (K_G), D242.3 (K_G), D270.3 (K_G), D298.3 (K_G), D326.3 (K_G), D354.3 (K_G), D382.3 (K_G), D410.3 (K_G), D438.3 (K_G), D466.3 (K_G), D494.3 (K_G), D522.3 (K_G), D550.3 (K_G), D578.3 (K_G), D606.3 (K_G), D634.3 (K_G), D662.3 (K_G), D690.3 (K_G), D718.3 (K_G), D746.3 (K_G), D774.3 (K_G)
COL_G_19: D19.3 (K_G), D47.3 (K_G), D75.3 (K_G), D103.3 (K_G), D131.3 (K_G), D159.3 (K_G), D187.3 (K_G), D215.3 (K_G), D243.3 (K_G), D271.3 (K_G), D299.3 (K_G), D327.3 (K_G), D355.3 (K_G), D383.3 (K_G), D411.3 (K_G), D439.3 (K_G), D467.3 (K_G), D495.3 (K_G), D523.3 (K_G), D551.3 (K_G), D579.3 (K_G), D607.3 (K_G), D635.3 (K_G), D663.3 (K_G), D691.3 (K_G), D719.3 (K_G), D747.3 (K_G), D775.3 (K_G)
COL_G_20: D20.3 (K_G), D48.3 (K_G), D76.3 (K_G), D104.3 (K_G), D132.3 (K_G), D160.3 (K_G), D188.3 (K_G), D216.3 (K_G), D244.3 (K_G), D272.3 (K_G), D300.3 (K_G), D328.3 (K_G), D356.3 (K_G), D384.3 (K_G), D412.3 (K_G), D440.3 (K_G), D468.3 (K_G), D496.3 (K_G), D524.3 (K_G), D552.3 (K_G), D580.3 (K_G), D608.3 (K_G), D636.3 (K_G), D664.3 (K_G), D692.3 (K_G), D720.3 (K_G), D748.3 (K_G), D776.3 (K_G)
COL_G_21: D21.3 (K_G), D49.3 (K_G), D77.3 (K_G), D105.3 (K_G), D133.3 (K_G), D161.3 (K_G), D189.3 (K_G), D217.3 (K_G), D245.3 (K_G), D273.3 (K_G), D301.3 (K_G), D329.3 (K_G), D357.3 (K_G), D385.3 (K_G), D413.3 (K_G), D441.3 (K_G), D469.3 (K_G), D497.3 (K_G), D525.3 (K_G), D553.3 (K_G), D581.3 (K_G), D609.3 (K_G), D637.3 (K_G), D665.3 (K_G), D693.3 (K_G), D721.3 (K_G), D749.3 (K_G), D777.3 (K_G)
COL_G_22: D22.3 (K_G), D50.3 (K_G), D78.3 (K_G), D106.3 (K_G), D134.3 (K_G), D162.3 (K_G), D190.3 (K_G), D218.3 (K_G), D246.3 (K_G), D274.3 (K_G), D302.3 (K_G), D330.3 (K_G), D358.3 (K_G), D386.3 (K_G), D414.3 (K_G), D442.3 (K_G), D470.3 (K_G), D498.3 (K_G), D526.3 (K_G), D554.3 (K_G), D582.3 (K_G), D610.3 (K_G), D638.3 (K_G), D666.3 (K_G), D694.3 (K_G), D722.3 (K_G), D750.3 (K_G), D778.3 (K_G)
COL_G_23: D23.3 (K_G), D51.3 (K_G), D79.3 (K_G), D107.3 (K_G), D135.3 (K_G), D163.3 (K_G), D191.3 (K_G), D219.3 (K_G), D247.3 (K_G), D275.3 (K_G), D303.3 (K_G), D331.3 (K_G), D359.3 (K_G), D387.3 (K_G), D415.3 (K_G), D443.3 (K_G), D471.3 (K_G), D499.3 (K_G), D527.3 (K_G), D555.3 (K_G), D583.3 (K_G), D611.3 (K_G), D639.3 (K_G), D667.3 (K_G), D695.3 (K_G), D723.3 (K_G), D751.3 (K_G), D779.3 (K_G)
COL_G_24: D24.3 (K_G), D52.3 (K_G), D80.3 (K_G), D108.3 (K_G), D136.3 (K_G), D164.3 (K_G), D192.3 (K_G), D220.3 (K_G), D248.3 (K_G), D276.3 (K_G), D304.3 (K_G), D332.3 (K_G), D360.3 (K_G), D388.3 (K_G), D416.3 (K_G), D444.3 (K_G), D472.3 (K_G), D500.3 (K_G), D528.3 (K_G), D556.3 (K_G), D584.3 (K_G), D612.3 (K_G), D640.3 (K_G), D668.3 (K_G), D696.3 (K_G), D724.3 (K_G), D752.3 (K_G), D780.3 (K_G)
COL_G_25: D25.3 (K_G), D53.3 (K_G), D81.3 (K_G), D109.3 (K_G), D137.3 (K_G), D165.3 (K_G), D193.3 (K_G), D221.3 (K_G), D249.3 (K_G), D277.3 (K_G), D305.3 (K_G), D333.3 (K_G), D361.3 (K_G), D389.3 (K_G), D417.3 (K_G), D445.3 (K_G), D473.3 (K_G), D501.3 (K_G), D529.3 (K_G), D557.3 (K_G), D585.3 (K_G), D613.3 (K_G), D641.3 (K_G), D669.3 (K_G), D697.3 (K_G), D725.3 (K_G), D753.3 (K_G), D781.3 (K_G)
COL_G_26: D26.3 (K_G), D54.3 (K_G), D82.3 (K_G), D110.3 (K_G), D138.3 (K_G), D166.3 (K_G), D194.3 (K_G), D222.3 (K_G), D250.3 (K_G), D278.3 (K_G), D306.3 (K_G), D334.3 (K_G), D362.3 (K_G), D390.3 (K_G), D418.3 (K_G), D446.3 (K_G), D474.3 (K_G), D502.3 (K_G), D530.3 (K_G), D558.3 (K_G), D586.3 (K_G), D614.3 (K_G), D642.3 (K_G), D670.3 (K_G), D698.3 (K_G), D726.3 (K_G), D754.3 (K_G), D782.3 (K_G)
COL_G_27: D27.3 (K_G), D55.3 (K_G), D83.3 (K_G), D111.3 (K_G), D139.3 (K_G), D167.3 (K_G), D195.3 (K_G), D223.3 (K_G), D251.3 (K_G), D279.3 (K_G), D307.3 (K_G), D335.3 (K_G), D363.3 (K_G), D391.3 (K_G), D419.3 (K_G), D447.3 (K_G), D475.3 (K_G), D503.3 (K_G), D531.3 (K_G), D559.3 (K_G), D587.3 (K_G), D615.3 (K_G), D643.3 (K_G), D671.3 (K_G), D699.3 (K_G), D727.3 (K_G), D755.3 (K_G), D783.3 (K_G)
COL_G_28: D28.3 (K_G), D56.3 (K_G), D84.3 (K_G), D112.3 (K_G), D140.3 (K_G), D168.3 (K_G), D196.3 (K_G), D224.3 (K_G), D252.3 (K_G), D280.3 (K_G), D308.3 (K_G), D336.3 (K_G), D364.3 (K_G), D392.3 (K_G), D420.3 (K_G), D448.3 (K_G), D476.3 (K_G), D504.3 (K_G), D532.3 (K_G), D560.3 (K_G), D588.3 (K_G), D616.3 (K_G), D644.3 (K_G), D672.3 (K_G), D700.3 (K_G), D728.3 (K_G), D756.3 (K_G), D784.3 (K_G)
COL_R_01: D1.2 (K_R), D29.2 (K_R), D57.2 (K_R), D85.2 (K_R), D113.2 (K_R), D141.2 (K_R), D169.2 (K_R), D197.2 (K_R), D225.2 (K_R), D253.2 (K_R), D281.2 (K_R), D309.2 (K_R), D337.2 (K_R), D365.2 (K_R), D393.2 (K_R), D421.2 (K_R), D449.2 (K_R), D477.2 (K_R), D505.2 (K_R), D533.2 (K_R), D561.2 (K_R), D589.2 (K_R), D617.2 (K_R), D645.2 (K_R), D673.2 (K_R), D701.2 (K_R), D729.2 (K_R), D757.2 (K_R)
COL_R_02: D2.2 (K_R), D30.2 (K_R), D58.2 (K_R), D86.2 (K_R), D114.2 (K_R), D142.2 (K_R), D170.2 (K_R), D198.2 (K_R), D226.2 (K_R), D254.2 (K_R), D282.2 (K_R), D310.2 (K_R), D338.2 (K_R), D366.2 (K_R), D394.2 (K_R), D422.2 (K_R), D450.2 (K_R), D478.2 (K_R), D506.2 (K_R), D534.2 (K_R), D562.2 (K_R), D590.2 (K_R), D618.2 (K_R), D646.2 (K_R), D674.2 (K_R), D702.2 (K_R), D730.2 (K_R), D758.2 (K_R)
COL_R_03: D3.2 (K_R), D31.2 (K_R), D59.2 (K_R), D87.2 (K_R), D115.2 (K_R), D143.2 (K_R), D171.2 (K_R), D199.2 (K_R), D227.2 (K_R), D255.2 (K_R), D283.2 (K_R), D311.2 (K_R), D339.2 (K_R), D367.2 (K_R), D395.2 (K_R), D423.2 (K_R), D451.2 (K_R), D479.2 (K_R), D507.2 (K_R), D535.2 (K_R), D563.2 (K_R), D591.2 (K_R), D619.2 (K_R), D647.2 (K_R), D675.2 (K_R), D703.2 (K_R), D731.2 (K_R), D759.2 (K_R)
COL_R_04: D4.2 (K_R), D32.2 (K_R), D60.2 (K_R), D88.2 (K_R), D116.2 (K_R), D144.2 (K_R), D172.2 (K_R), D200.2 (K_R), D228.2 (K_R), D256.2 (K_R), D284.2 (K_R), D312.2 (K_R), D340.2 (K_R), D368.2 (K_R), D396.2 (K_R), D424.2 (K_R), D452.2 (K_R), D480.2 (K_R), D508.2 (K_R), D536.2 (K_R), D564.2 (K_R), D592.2 (K_R), D620.2 (K_R), D648.2 (K_R), D676.2 (K_R), D704.2 (K_R), D732.2 (K_R), D760.2 (K_R)
COL_R_05: D5.2 (K_R), D33.2 (K_R), D61.2 (K_R), D89.2 (K_R), D117.2 (K_R), D145.2 (K_R), D173.2 (K_R), D201.2 (K_R), D229.2 (K_R), D257.2 (K_R), D285.2 (K_R), D313.2 (K_R), D341.2 (K_R), D369.2 (K_R), D397.2 (K_R), D425.2 (K_R), D453.2 (K_R), D481.2 (K_R), D509.2 (K_R), D537.2 (K_R), D565.2 (K_R), D593.2 (K_R), D621.2 (K_R), D649.2 (K_R), D677.2 (K_R), D705.2 (K_R), D733.2 (K_R), D761.2 (K_R)
COL_R_06: D6.2 (K_R), D34.2 (K_R), D62.2 (K_R), D90.2 (K_R), D118.2 (K_R), D146.2 (K_R), D174.2 (K_R), D202.2 (K_R), D230.2 (K_R), D258.2 (K_R), D286.2 (K_R), D314.2 (K_R), D342.2 (K_R), D370.2 (K_R), D398.2 (K_R), D426.2 (K_R), D454.2 (K_R), D482.2 (K_R), D510.2 (K_R), D538.2 (K_R), D566.2 (K_R), D594.2 (K_R), D622.2 (K_R), D650.2 (K_R), D678.2 (K_R), D706.2 (K_R), D734.2 (K_R), D762.2 (K_R)
COL_R_07: D7.2 (K_R), D35.2 (K_R), D63.2 (K_R), D91.2 (K_R), D119.2 (K_R), D147.2 (K_R), D175.2 (K_R), D203.2 (K_R), D231.2 (K_R), D259.2 (K_R), D287.2 (K_R), D315.2 (K_R), D343.2 (K_R), D371.2 (K_R), D399.2 (K_R), D427.2 (K_R), D455.2 (K_R), D483.2 (K_R), D511.2 (K_R), D539.2 (K_R), D567.2 (K_R), D595.2 (K_R), D623.2 (K_R), D651.2 (K_R), D679.2 (K_R), D707.2 (K_R), D735.2 (K_R), D763.2 (K_R)
COL_R_08: D8.2 (K_R), D36.2 (K_R), D64.2 (K_R), D92.2 (K_R), D120.2 (K_R), D148.2 (K_R), D176.2 (K_R), D204.2 (K_R), D232.2 (K_R), D260.2 (K_R), D288.2 (K_R), D316.2 (K_R), D344.2 (K_R), D372.2 (K_R), D400.2 (K_R), D428.2 (K_R), D456.2 (K_R), D484.2 (K_R), D512.2 (K_R), D540.2 (K_R), D568.2 (K_R), D596.2 (K_R), D624.2 (K_R), D652.2 (K_R), D680.2 (K_R), D708.2 (K_R), D736.2 (K_R), D764.2 (K_R)
COL_R_09: D9.2 (K_R), D37.2 (K_R), D65.2 (K_R), D93.2 (K_R), D121.2 (K_R), D149.2 (K_R), D177.2 (K_R), D205.2 (K_R), D233.2 (K_R), D261.2 (K_R), D289.2 (K_R), D317.2 (K_R), D345.2 (K_R), D373.2 (K_R), D401.2 (K_R), D429.2 (K_R), D457.2 (K_R), D485.2 (K_R), D513.2 (K_R), D541.2 (K_R), D569.2 (K_R), D597.2 (K_R), D625.2 (K_R), D653.2 (K_R), D681.2 (K_R), D709.2 (K_R), D737.2 (K_R), D765.2 (K_R)
COL_R_10: D10.2 (K_R), D38.2 (K_R), D66.2 (K_R), D94.2 (K_R), D122.2 (K_R), D150.2 (K_R), D178.2 (K_R), D206.2 (K_R), D234.2 (K_R), D262.2 (K_R), D290.2 (K_R), D318.2 (K_R), D346.2 (K_R), D374.2 (K_R), D402.2 (K_R), D430.2 (K_R), D458.2 (K_R), D486.2 (K_R), D514.2 (K_R), D542.2 (K_R), D570.2 (K_R), D598.2 (K_R), D626.2 (K_R), D654.2 (K_R), D682.2 (K_R), D710.2 (K_R), D738.2 (K_R), D766.2 (K_R)
COL_R_11: D11.2 (K_R), D39.2 (K_R), D67.2 (K_R), D95.2 (K_R), D123.2 (K_R), D151.2 (K_R), D179.2 (K_R), D207.2 (K_R), D235.2 (K_R), D263.2 (K_R), D291.2 (K_R), D319.2 (K_R), D347.2 (K_R), D375.2 (K_R), D403.2 (K_R), D431.2 (K_R), D459.2 (K_R), D487.2 (K_R), D515.2 (K_R), D543.2 (K_R), D571.2 (K_R), D599.2 (K_R), D627.2 (K_R), D655.2 (K_R), D683.2 (K_R), D711.2 (K_R), D739.2 (K_R), D767.2 (K_R)
COL_R_12: D12.2 (K_R), D40.2 (K_R), D68.2 (K_R), D96.2 (K_R), D124.2 (K_R), D152.2 (K_R), D180.2 (K_R), D208.2 (K_R), D236.2 (K_R), D264.2 (K_R), D292.2 (K_R), D320.2 (K_R), D348.2 (K_R), D376.2 (K_R), D404.2 (K_R), D432.2 (K_R), D460.2 (K_R), D488.2 (K_R), D516.2 (K_R), D544.2 (K_R), D572.2 (K_R), D600.2 (K_R), D628.2 (K_R), D656.2 (K_R), D684.2 (K_R), D712.2 (K_R), D740.2 (K_R), D768.2 (K_R)
COL_R_13: D13.2 (K_R), D41.2 (K_R), D69.2 (K_R), D97.2 (K_R), D125.2 (K_R), D153.2 (K_R), D181.2 (K_R), D209.2 (K_R), D237.2 (K_R), D265.2 (K_R), D293.2 (K_R), D321.2 (K_R), D349.2 (K_R), D377.2 (K_R), D405.2 (K_R), D433.2 (K_R), D461.2 (K_R), D489.2 (K_R), D517.2 (K_R), D545.2 (K_R), D573.2 (K_R), D601.2 (K_R), D629.2 (K_R), D657.2 (K_R), D685.2 (K_R), D713.2 (K_R), D741.2 (K_R), D769.2 (K_R)
COL_R_14: D14.2 (K_R), D42.2 (K_R), D70.2 (K_R), D98.2 (K_R), D126.2 (K_R), D154.2 (K_R), D182.2 (K_R), D210.2 (K_R), D238.2 (K_R), D266.2 (K_R), D294.2 (K_R), D322.2 (K_R), D350.2 (K_R), D378.2 (K_R), D406.2 (K_R), D434.2 (K_R), D462.2 (K_R), D490.2 (K_R), D518.2 (K_R), D546.2 (K_R), D574.2 (K_R), D602.2 (K_R), D630.2 (K_R), D658.2 (K_R), D686.2 (K_R), D714.2 (K_R), D742.2 (K_R), D770.2 (K_R)
COL_R_15: D15.2 (K_R), D43.2 (K_R), D71.2 (K_R), D99.2 (K_R), D127.2 (K_R), D155.2 (K_R), D183.2 (K_R), D211.2 (K_R), D239.2 (K_R), D267.2 (K_R), D295.2 (K_R), D323.2 (K_R), D351.2 (K_R), D379.2 (K_R), D407.2 (K_R), D435.2 (K_R), D463.2 (K_R), D491.2 (K_R), D519.2 (K_R), D547.2 (K_R), D575.2 (K_R), D603.2 (K_R), D631.2 (K_R), D659.2 (K_R), D687.2 (K_R), D715.2 (K_R), D743.2 (K_R), D771.2 (K_R)
COL_R_16: D16.2 (K_R), D44.2 (K_R), D72.2 (K_R), D100.2 (K_R), D128.2 (K_R), D156.2 (K_R), D184.2 (K_R), D212.2 (K_R), D240.2 (K_R), D268.2 (K_R), D296.2 (K_R), D324.2 (K_R), D352.2 (K_R), D380.2 (K_R), D408.2 (K_R), D436.2 (K_R), D464.2 (K_R), D492.2 (K_R), D520.2 (K_R), D548.2 (K_R), D576.2 (K_R), D604.2 (K_R), D632.2 (K_R), D660.2 (K_R), D688.2 (K_R), D716.2 (K_R), D744.2 (K_R), D772.2 (K_R)
COL_R_17: D17.2 (K_R), D45.2 (K_R), D73.2 (K_R), D101.2 (K_R), D129.2 (K_R), D157.2 (K_R), D185.2 (K_R), D213.2 (K_R), D241.2 (K_R), D269.2 (K_R), D297.2 (K_R), D325.2 (K_R), D353.2 (K_R), D381.2 (K_R), D409.2 (K_R), D437.2 (K_R), D465.2 (K_R), D493.2 (K_R), D521.2 (K_R), D549.2 (K_R), D577.2 (K_R), D605.2 (K_R), D633.2 (K_R), D661.2 (K_R), D689.2 (K_R), D717.2 (K_R), D745.2 (K_R), D773.2 (K_R)
COL_R_18: D18.2 (K_R), D46.2 (K_R), D74.2 (K_R), D102.2 (K_R), D130.2 (K_R), D158.2 (K_R), D186.2 (K_R), D214.2 (K_R), D242.2 (K_R), D270.2 (K_R), D298.2 (K_R), D326.2 (K_R), D354.2 (K_R), D382.2 (K_R), D410.2 (K_R), D438.2 (K_R), D466.2 (K_R), D494.2 (K_R), D522.2 (K_R), D550.2 (K_R), D578.2 (K_R), D606.2 (K_R), D634.2 (K_R), D662.2 (K_R), D690.2 (K_R), D718.2 (K_R), D746.2 (K_R), D774.2 (K_R)
COL_R_19: D19.2 (K_R), D47.2 (K_R), D75.2 (K_R), D103.2 (K_R), D131.2 (K_R), D159.2 (K_R), D187.2 (K_R), D215.2 (K_R), D243.2 (K_R), D271.2 (K_R), D299.2 (K_R), D327.2 (K_R), D355.2 (K_R), D383.2 (K_R), D411.2 (K_R), D439.2 (K_R), D467.2 (K_R), D495.2 (K_R), D523.2 (K_R), D551.2 (K_R), D579.2 (K_R), D607.2 (K_R), D635.2 (K_R), D663.2 (K_R), D691.2 (K_R), D719.2 (K_R), D747.2 (K_R), D775.2 (K_R)
COL_R_20: D20.2 (K_R), D48.2 (K_R), D76.2 (K_R), D104.2 (K_R), D132.2 (K_R), D160.2 (K_R), D188.2 (K_R), D216.2 (K_R), D244.2 (K_R), D272.2 (K_R), D300.2 (K_R), D328.2 (K_R), D356.2 (K_R), D384.2 (K_R), D412.2 (K_R), D440.2 (K_R), D468.2 (K_R), D496.2 (K_R), D524.2 (K_R), D552.2 (K_R), D580.2 (K_R), D608.2 (K_R), D636.2 (K_R), D664.2 (K_R), D692.2 (K_R), D720.2 (K_R), D748.2 (K_R), D776.2 (K_R)
COL_R_21: D21.2 (K_R), D49.2 (K_R), D77.2 (K_R), D105.2 (K_R), D133.2 (K_R), D161.2 (K_R), D189.2 (K_R), D217.2 (K_R), D245.2 (K_R), D273.2 (K_R), D301.2 (K_R), D329.2 (K_R), D357.2 (K_R), D385.2 (K_R), D413.2 (K_R), D441.2 (K_R), D469.2 (K_R), D497.2 (K_R), D525.2 (K_R), D553.2 (K_R), D581.2 (K_R), D609.2 (K_R), D637.2 (K_R), D665.2 (K_R), D693.2 (K_R), D721.2 (K_R), D749.2 (K_R), D777.2 (K_R)
COL_R_22: D22.2 (K_R), D50.2 (K_R), D78.2 (K_R), D106.2 (K_R), D134.2 (K_R), D162.2 (K_R), D190.2 (K_R), D218.2 (K_R), D246.2 (K_R), D274.2 (K_R), D302.2 (K_R), D330.2 (K_R), D358.2 (K_R), D386.2 (K_R), D414.2 (K_R), D442.2 (K_R), D470.2 (K_R), D498.2 (K_R), D526.2 (K_R), D554.2 (K_R), D582.2 (K_R), D610.2 (K_R), D638.2 (K_R), D666.2 (K_R), D694.2 (K_R), D722.2 (K_R), D750.2 (K_R), D778.2 (K_R)
COL_R_23: D23.2 (K_R), D51.2 (K_R), D79.2 (K_R), D107.2 (K_R), D135.2 (K_R), D163.2 (K_R), D191.2 (K_R), D219.2 (K_R), D247.2 (K_R), D275.2 (K_R), D303.2 (K_R), D331.2 (K_R), D359.2 (K_R), D387.2 (K_R), D415.2 (K_R), D443.2 (K_R), D471.2 (K_R), D499.2 (K_R), D527.2 (K_R), D555.2 (K_R), D583.2 (K_R), D611.2 (K_R), D639.2 (K_R), D667.2 (K_R), D695.2 (K_R), D723.2 (K_R), D751.2 (K_R), D779.2 (K_R)
COL_R_24: D24.2 (K_R), D52.2 (K_R), D80.2 (K_R), D108.2 (K_R), D136.2 (K_R), D164.2 (K_R), D192.2 (K_R), D220.2 (K_R), D248.2 (K_R), D276.2 (K_R), D304.2 (K_R), D332.2 (K_R), D360.2 (K_R), D388.2 (K_R), D416.2 (K_R), D444.2 (K_R), D472.2 (K_R), D500.2 (K_R), D528.2 (K_R), D556.2 (K_R), D584.2 (K_R), D612.2 (K_R), D640.2 (K_R), D668.2 (K_R), D696.2 (K_R), D724.2 (K_R), D752.2 (K_R), D780.2 (K_R)
COL_R_25: D25.2 (K_R), D53.2 (K_R), D81.2 (K_R), D109.2 (K_R), D137.2 (K_R), D165.2 (K_R), D193.2 (K_R), D221.2 (K_R), D249.2 (K_R), D277.2 (K_R), D305.2 (K_R), D333.2 (K_R), D361.2 (K_R), D389.2 (K_R), D417.2 (K_R), D445.2 (K_R), D473.2 (K_R), D501.2 (K_R), D529.2 (K_R), D557.2 (K_R), D585.2 (K_R), D613.2 (K_R), D641.2 (K_R), D669.2 (K_R), D697.2 (K_R), D725.2 (K_R), D753.2 (K_R), D781.2 (K_R)
COL_R_26: D26.2 (K_R), D54.2 (K_R), D82.2 (K_R), D110.2 (K_R), D138.2 (K_R), D166.2 (K_R), D194.2 (K_R), D222.2 (K_R), D250.2 (K_R), D278.2 (K_R), D306.2 (K_R), D334.2 (K_R), D362.2 (K_R), D390.2 (K_R), D418.2 (K_R), D446.2 (K_R), D474.2 (K_R), D502.2 (K_R), D530.2 (K_R), D558.2 (K_R), D586.2 (K_R), D614.2 (K_R), D642.2 (K_R), D670.2 (K_R), D698.2 (K_R), D726.2 (K_R), D754.2 (K_R), D782.2 (K_R)
COL_R_27: D27.2 (K_R), D55.2 (K_R), D83.2 (K_R), D111.2 (K_R), D139.2 (K_R), D167.2 (K_R), D195.2 (K_R), D223.2 (K_R), D251.2 (K_R), D279.2 (K_R), D307.2 (K_R), D335.2 (K_R), D363.2 (K_R), D391.2 (K_R), D419.2 (K_R), D447.2 (K_R), D475.2 (K_R), D503.2 (K_R), D531.2 (K_R), D559.2 (K_R), D587.2 (K_R), D615.2 (K_R), D643.2 (K_R), D671.2 (K_R), D699.2 (K_R), D727.2 (K_R), D755.2 (K_R), D783.2 (K_R)
COL_R_28: D28.2 (K_R), D56.2 (K_R), D84.2 (K_R), D112.2 (K_R), D140.2 (K_R), D168.2 (K_R), D196.2 (K_R), D224.2 (K_R), D252.2 (K_R), D280.2 (K_R), D308.2 (K_R), D336.2 (K_R), D364.2 (K_R), D392.2 (K_R), D420.2 (K_R), D448.2 (K_R), D476.2 (K_R), D504.2 (K_R), D532.2 (K_R), D560.2 (K_R), D588.2 (K_R), D616.2 (K_R), D644.2 (K_R), D672.2 (K_R), D700.2 (K_R), D728.2 (K_R), D756.2 (K_R), D784.2 (K_R)
ROW_01_ANODE: D1.1 (A), D2.1 (A), D3.1 (A), D4.1 (A), D5.1 (A), D6.1 (A), D7.1 (A), D8.1 (A), D9.1 (A), D10.1 (A), D11.1 (A), D12.1 (A), D13.1 (A), D14.1 (A), D15.1 (A), D16.1 (A), D17.1 (A), D18.1 (A), D19.1 (A), D20.1 (A), D21.1 (A), D22.1 (A), D23.1 (A), D24.1 (A), D25.1 (A), D26.1 (A), D27.1 (A), D28.1 (A)
ROW_02_ANODE: D29.1 (A), D30.1 (A), D31.1 (A), D32.1 (A), D33.1 (A), D34.1 (A), D35.1 (A), D36.1 (A), D37.1 (A), D38.1 (A), D39.1 (A), D40.1 (A), D41.1 (A), D42.1 (A), D43.1 (A), D44.1 (A), D45.1 (A), D46.1 (A), D47.1 (A), D48.1 (A), D49.1 (A), D50.1 (A), D51.1 (A), D52.1 (A), D53.1 (A), D54.1 (A), D55.1 (A), D56.1 (A)
ROW_03_ANODE: D57.1 (A), D58.1 (A), D59.1 (A), D60.1 (A), D61.1 (A), D62.1 (A), D63.1 (A), D64.1 (A), D65.1 (A), D66.1 (A), D67.1 (A), D68.1 (A), D69.1 (A), D70.1 (A), D71.1 (A), D72.1 (A), D73.1 (A), D74.1 (A), D75.1 (A), D76.1 (A), D77.1 (A), D78.1 (A), D79.1 (A), D80.1 (A), D81.1 (A), D82.1 (A), D83.1 (A), D84.1 (A)
ROW_04_ANODE: D85.1 (A), D86.1 (A), D87.1 (A), D88.1 (A), D89.1 (A), D90.1 (A), D91.1 (A), D92.1 (A), D93.1 (A), D94.1 (A), D95.1 (A), D96.1 (A), D97.1 (A), D98.1 (A), D99.1 (A), D100.1 (A), D101.1 (A), D102.1 (A), D103.1 (A), D104.1 (A), D105.1 (A), D106.1 (A), D107.1 (A), D108.1 (A), D109.1 (A), D110.1 (A), D111.1 (A), D112.1 (A)
ROW_05_ANODE: D113.1 (A), D114.1 (A), D115.1 (A), D116.1 (A), D117.1 (A), D118.1 (A), D119.1 (A), D120.1 (A), D121.1 (A), D122.1 (A), D123.1 (A), D124.1 (A), D125.1 (A), D126.1 (A), D127.1 (A), D128.1 (A), D129.1 (A), D130.1 (A), D131.1 (A), D132.1 (A), D133.1 (A), D134.1 (A), D135.1 (A), D136.1 (A), D137.1 (A), D138.1 (A), D139.1 (A), D140.1 (A)
ROW_06_ANODE: D141.1 (A), D142.1 (A), D143.1 (A), D144.1 (A), D145.1 (A), D146.1 (A), D147.1 (A), D148.1 (A), D149.1 (A), D150.1 (A), D151.1 (A), D152.1 (A), D153.1 (A), D154.1 (A), D155.1 (A), D156.1 (A), D157.1 (A), D158.1 (A), D159.1 (A), D160.1 (A), D161.1 (A), D162.1 (A), D163.1 (A), D164.1 (A), D165.1 (A), D166.1 (A), D167.1 (A), D168.1 (A)
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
